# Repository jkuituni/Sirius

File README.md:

A very simple 6502 based single board computer with just about as much chips as is needed as minimum.

- 6502 CPU
- 8kB EPROM for Firmware
- Up to 48kB RAM comprised from maximum of 6x 8kB SRAM chips
- 8kB reserved I/O area with 1kB blocks having the following;
  - 6551 ACIA for rs232 with max233 level translator
- Two TTL decoder chips for memory mapping.

Initial design of this board was drawn by hand to pieces of paper some 25+ years ago. What you see here is 
an attempt to capture that design into digital form using KiCAD with intentionally not making changes to it if possible.

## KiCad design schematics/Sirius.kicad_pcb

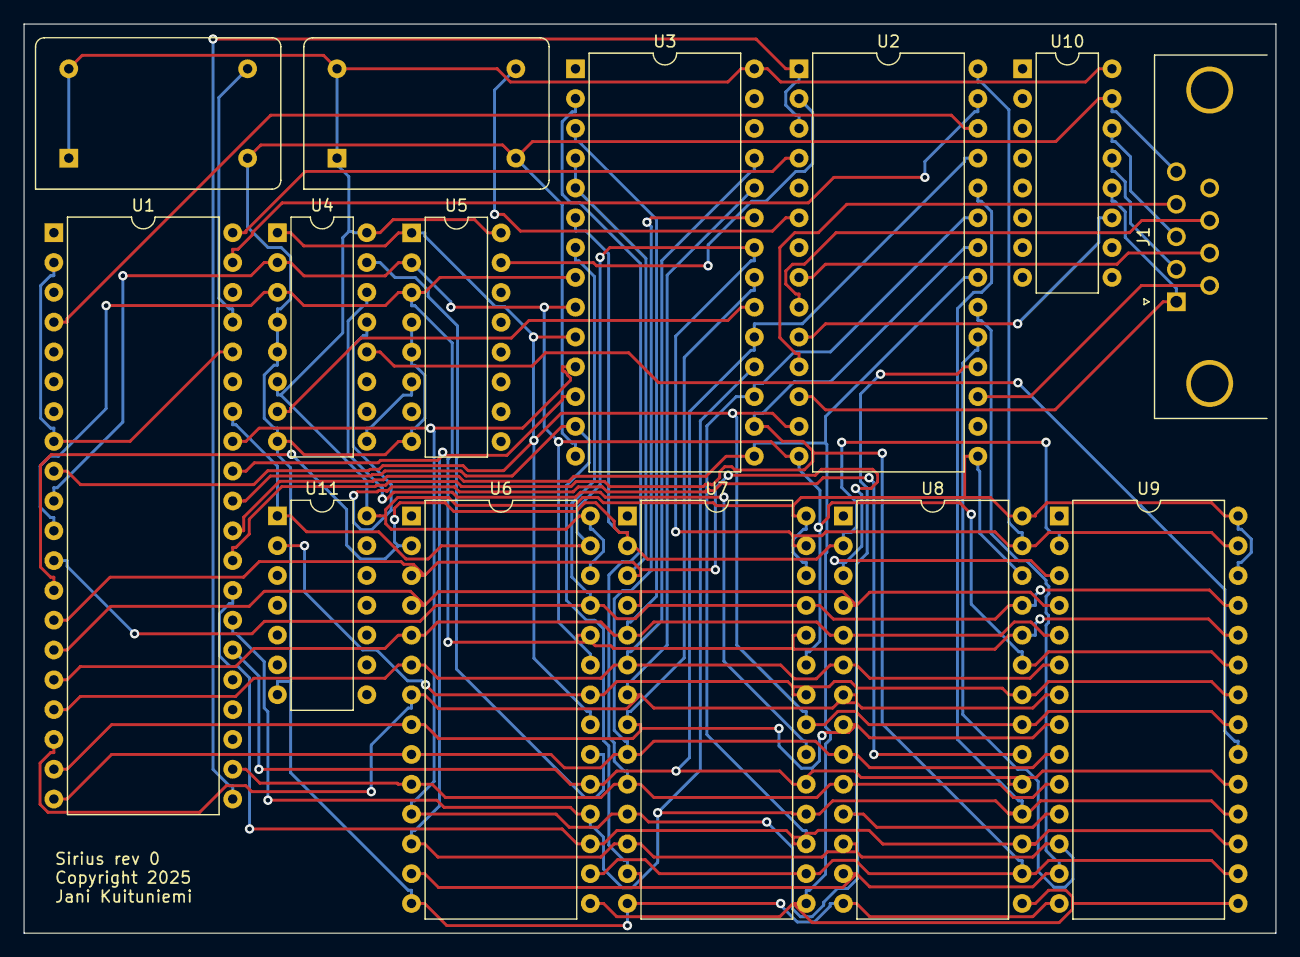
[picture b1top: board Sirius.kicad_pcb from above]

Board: 2 copper layers, 106.7 x 77.5 mm, 14 parts (0 on the bottom side), 47 nets.

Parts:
J1: DE9_Plug; DSUB-9_Male_Horizontal_P2.77x2.84mm_EdgePinOffset4.94mm_Hou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
U1: W65C02SxP; DIP-40_W15.24mm
U2: W65C51NxP; DIP-28_W15.24mm
U3: 2764; DIP-28_W15.24mm
U4, U5: 74LS138; DIP-16_W7.62mm
U6, U7, U8, U9: DIP-28_W15.24mm
U10: MAX232; DIP-16_W7.62mm
U11: 7404; DIP-14_W7.62mm
X1, X2: TFT680; Oscillator_DIP-14

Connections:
/D0: U1.33 (D0), U2.18 (D0), U3.11 (D0), U6.11 (I/O0), U7.11 (I/O0), U8.11 (I/O0), U9.11 (I/O0)
/D1: U1.32 (D1), U2.19 (D1), U3.12 (D1), U6.12 (I/O1), U7.12 (I/O1), U8.12 (I/O1), U9.12 (I/O1)
/D2: U1.31 (D2), U2.20 (D2), U3.13 (D2), U6.13 (I/O2), U7.13 (I/O2), U8.13 (I/O2), U9.13 (I/O2)
/D3: U1.30 (D3), U2.21 (D3), U3.15 (D3), U6.15 (I/O3), U7.15 (I/O3), U8.15 (I/O3), U9.15 (I/O3)
/D4: U1.29 (D4), U2.22 (D4), U3.16 (D4), U6.16 (I/O4), U7.16 (I/O4), U8.16 (I/O4), U9.16 (I/O4)
/D5: U1.28 (D5), U2.23 (D5), U3.17 (D5), U6.17 (I/O5), U7.17 (I/O5), U8.17 (I/O5), U9.17 (I/O5)
/D6: U1.27 (D6), U2.24 (D6), U3.18 (D6), U6.18 (I/O6), U7.18 (I/O6), U8.18 (I/O6), U9.18 (I/O6)
/D7: U1.26 (D7), U2.25 (D7), U3.19 (D7), U6.19 (I/O7), U7.19 (I/O7), U8.19 (I/O7), U9.19 (I/O7)
A0: U1.9 (A0), U2.13 (RS0), U3.10 (A0), U4.1 (A0), U5.1 (A0), U6.21 (A0), U7.21 (A0), U8.21 (A0), U9.21 (A0)
A1: U1.10 (A1), U2.14 (RS1), U3.9 (A1), U4.2 (A1), U5.2 (A1), U6.23 (A1), U7.23 (A1), U8.23 (A1), U9.23 (A1)
A2: U1.11 (A2), U3.8 (A2), U4.3 (A2), U5.3 (A2), U6.24 (A2), U7.24 (A2), U8.24 (A2), U9.24 (A2)
A3: U1.12 (A3), U3.7 (A3), U6.25 (A3), U7.25 (A3), U8.25 (A3), U9.25 (A3)
A4: U1.13 (A4), U3.6 (A4), U6.2 (A4), U7.2 (A4), U8.2 (A4), U9.2 (A4)
A5: U1.14 (A5), U3.4 (A6), U3.5 (A5), U6.3 (A5), U7.3 (A5), U8.3 (A5), U9.3 (A5)
A6: U1.15 (A6), U6.4 (A6), U7.4 (A6), U8.4 (A6), U9.4 (A6)
A7: U1.16 (A7), U3.3 (A7), U6.5 (A7), U7.5 (A7), U8.5 (A7), U9.5 (A7)
A8: U1.17 (A8), U3.25 (A8), U6.6 (A8), U7.6 (A8), U8.6 (A8), U9.6 (A8)
A9: U1.18 (A9), U3.24 (A9), U6.7 (A9), U7.7 (A9), U8.7 (A9), U9.7 (A9)
A10: U1.19 (A10), U3.21 (A10), U6.8 (A10), U7.8 (A10), U8.8 (A10), U9.8 (A10)
A11: U1.20 (A11), U3.23 (A11), U6.9 (A11), U7.9 (A11), U8.9 (A11), U9.9 (A11)
A12: U1.22 (A12), U3.2 (A12), U6.10 (A12), U7.10 (A12), U8.10 (A12), U9.10 (A12)
GND: J1.5, U3.14 (GND), U4.4 (E1), U4.5 (E2), U4.8 (GND), U5.4 (E1), U5.5 (E2), U5.8 (GND), U6.14 (GND), U7.14 (GND), U8.14 (GND), U9.14 (GND), U10.15 (GND), U11.7 (GND), X1.7 (GND), X2.7 (GND)
unnamed: U1.34 (R/~W), U2.28 (R/~W), U3.22 (~OE), U6.27 (/WE), U7.27 (/WE), U8.27 (/WE), U9.27 (/WE), U11.1
unnamed: U1.4 (~IRQ), U2.26 (~IRQ)
unnamed: U1.40 (~RES), U2.4 (~RES)
unnamed: U1.37 (ϕ0), X1.8 (OUT)
unnamed: U1.39 (ϕ2), U2.27 (ϕ2)
unnamed: U2.2 (CS1), U5.15 (O0)
unnamed: U2.6 (XTAL1), X2.8 (OUT)
unnamed: J1.8, U2.9 (~CTS)
unnamed: J1.6, U2.17 (~DSR)
unnamed: J1.4, U2.11 (~DTR)
unnamed: J1.7, U2.8 (~RTS)
unnamed: U3.20 (~CE), U4.7 (O7)
unnamed: U4.15 (O0), U6.20 (/CE1)
unnamed: U4.14 (O1), U7.20 (/CE1)
unnamed: U4.13 (O2), U8.20 (/CE1)
unnamed: U4.12 (O3), U9.20 (/CE1)
unnamed: U4.9 (O6), U5.6 (E3)
unnamed: U6.22 (/OE), U7.22 (/OE), U8.22 (/OE), U9.22 (/OE), U11.2
unnamed: J1.2, U10.13 (R1IN)
unnamed: J1.1, U2.12 (RxD), U2.16 (~DCD), U10.12 (R1OUT)
unnamed: U2.10 (TxD), U10.11 (T1IN)
unnamed: J1.3, U10.14 (T1OUT)
VCC: U2.15 (VCC), U3.28 (VCC), U4.6 (E3), U4.16 (VCC), U5.16 (VCC), U6.26 (CE2), U6.28 (Vcc), U7.26 (CE2), U7.28 (Vcc), U8.26 (CE2), U8.28 (Vcc), U9.26 (CE2), U9.28 (Vcc), U10.16 (VCC), U11.14 (VCC), X1.1 (EN), X1.14 (Vcc), X2.1 (EN), X2.14 (Vcc)
VDD: U1.2 (RDY), U1.8 (VDD), U1.36 (BE)
VSS: U1.21 (VSS), U2.1 (VSS), U2.3 (~CS2)

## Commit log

2023-10-23 Initial commit with very much incomplete work-in-progress schematics.
2023-10-23 Added README.md file.
2023-10-23 A small update to README.
2023-10-23 Clarification to the specifications on the README.
2023-10-23 Re-worked schematics. Still lot of work to be done.
2023-10-23 Adjusted the README.
2023-10-23 Re-wording.
2023-10-24 Added RAM along with connectivity. Still issues with using the Bus.
2023-10-24 Added rs232 parts. Still some caps to add.
2023-10-24 Added N/C (No Connect) flags.
2023-10-24 Added datasheets for the chips used.
2023-10-24 Removed unnecessary file.
2023-10-24 Added WDC 65c02S datasheet.
2023-10-24 Added some more signal handling and caps for rs232 infterface's max232 level shifter.
2023-10-24 Minor tweaks to signals and PCB layout.
2024-02-22 Fixed the Bus connetions. Added a forgotten 7404 inverter for R/W signal and did a autorouted board.
2024-02-26 Add 7404 inverter datasheet.
2025-01-19 Minor alterations to PCB layout.
2025-02-06 Some ERC and DRC fixes.

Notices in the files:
schematics/Sirius.kicad_pcb:
Copyright 2025
